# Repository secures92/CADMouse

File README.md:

CADMouse
========

fully 3D printable CAD-Mouse with host software for solidworks.

CAD-Mouse is connected as Joystick. Windows host software translates Axis movements to Solidworks view translation commands.
(Any standard joystick could be use)

Thingiverse: http://www.thingiverse.com/thing:260830
Warning : some parts have been upgraded, check latest version on github.

Video
------
New top spring and added translate / zoom :

Original demo

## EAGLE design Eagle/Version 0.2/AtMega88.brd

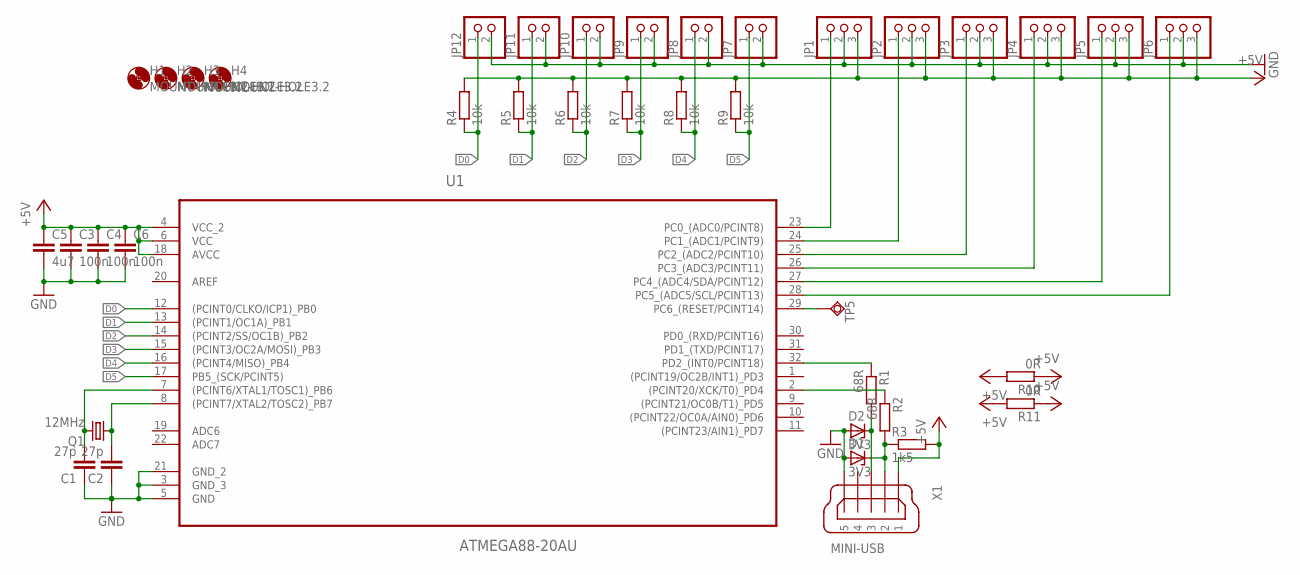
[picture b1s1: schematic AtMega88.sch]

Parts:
C1, C2: 27p; C0805
C3, C4, C6: 100n; C0805
C5: 4u7; C0805
D1, D2: 3V3; SOT23
H1, H2, H3, H4: MOUNT-HOLE3.2; 3,2
JP1, JP2, JP3, JP4, JP5, JP6: PINHD-1X3; 1X03
JP7, JP8, JP9, JP10, JP11, JP12: PINHD-1X2; 1X02
Q1: 12MHz; CSM-7X-DU
R1, R2: 68R; R1206
R3: 1k5; R1206
R4, R5, R6, R7, R8, R9: 10k; R1206
R10, R11: 0R; R1206
TP5: TPSQTP20SQ; TP20SQ
U1: ATMEGA88-20AU; QFP80P900X900X120-32N
X1: MINI-USB; UX60A-MB-5ST

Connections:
+5V: C3.1, C4.1, C5.1, C6.1, JP1.3, JP2.3, JP3.3, JP4.3, JP5.3, JP6.3, R3.2, R4.2, R5.2, R6.2, R7.2, R8.2, R9.2, R10.1, R10.2, R11.1, R11.2, U1.4 (VCC_2), U1.6 (VCC), U1.18 (AVCC), X1.1
A0: JP1.1, U1.23 (PC0_(ADC0/PCINT8))
A1: JP2.1, U1.24 (PC1_(ADC1/PCINT9))
A2: JP3.1, U1.25 (PC2_(ADC2/PCINT10))
A3: JP4.1, U1.26 (PC3_(ADC3/PCINT11))
A4: JP5.1, U1.27 (PC4_(ADC4/SDA/PCINT12))
A5: JP6.1, U1.28 (PC5_(ADC5/SCL/PCINT13))
D0: JP12.1, R4.1, U1.12 ((PCINT0/CLKO/ICP1)_PB0)
D1: JP11.1, R5.1, U1.13 ((PCINT1/OC1A)_PB1)
D2: JP10.1, R6.1, U1.14 ((PCINT2/SS/OC1B)_PB2)
D3: JP9.1, R7.1, U1.15 ((PCINT3/OC2A/MOSI)_PB3)
D4: JP8.1, R8.1, U1.16 ((PCINT4/MISO)_PB4)
D5: JP7.1, R9.1, U1.17 (PB5_(SCK/PCINT5))
GND: C1.1, C2.1, C3.2, C4.2, C5.2, C6.2, D1.1 (A), D2.1 (A), JP1.2, JP2.2, JP3.2, JP4.2, JP5.2, JP6.2, JP7.2, JP8.2, JP9.2, JP10.2, JP11.2, JP12.2, U1.3 (GND_3), U1.5 (GND), U1.21 (GND_2), X1.5
unnamed: C1.2, Q1.2, U1.7 ((PCINT6/XTAL1/TOSC1)_PB6)
unnamed: C2.2, Q1.1, U1.8 ((PCINT7/XTAL2/TOSC2)_PB7)
unnamed: R1.1, U1.32 (PD2_(INT0/PCINT18))
unnamed: R2.1, U1.2 ((PCINT20/XCK/T0)_PD4)
unnamed: D2.3 (C), R1.2, X1.3
unnamed: D1.3 (C), R2.2, R3.1, X1.2
unnamed: TP5.TP, U1.29 (PC6_(RESET/PCINT14))

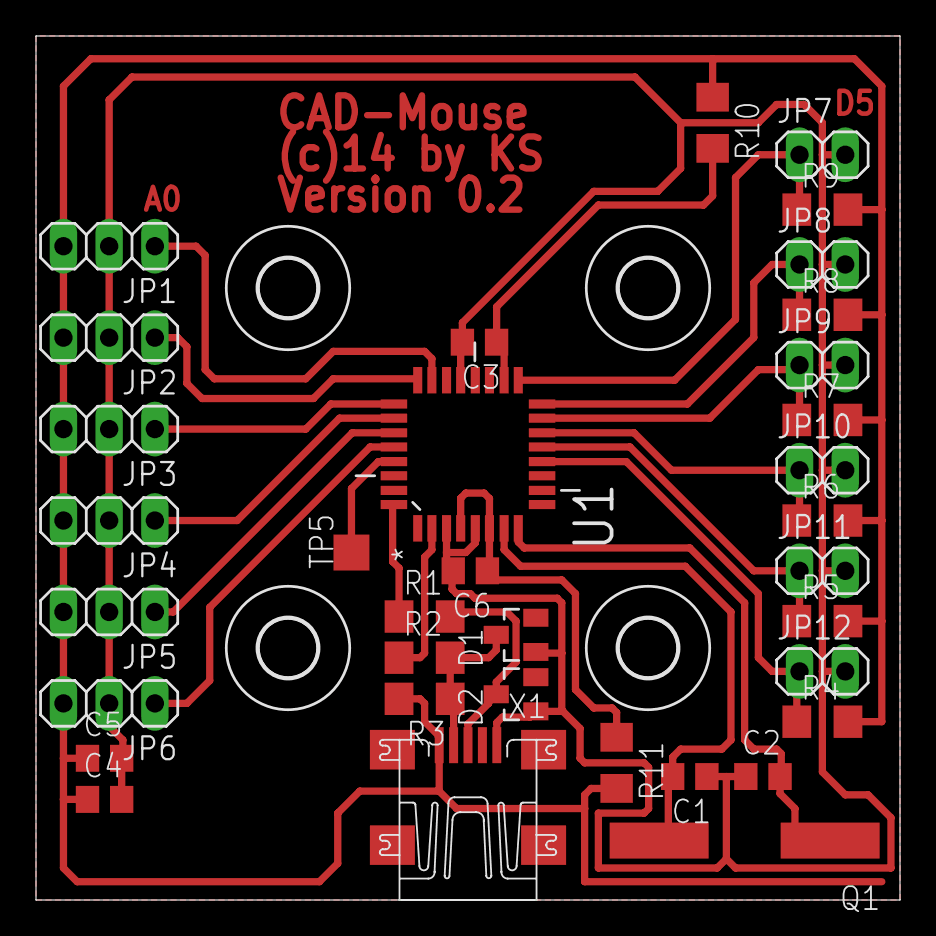
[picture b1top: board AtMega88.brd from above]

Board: 2 copper layers, 48.0 x 48.0 mm, 39 parts (0 on the bottom side), 21 nets.

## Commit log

2014-03-01 init
2014-03-01 media
2014-03-03 Electronics Version 0.2
    Updated Electronics to Version 0.2
2014-05-08 add Z axis to zoom, make it work for every version of solidworks, improve smoothness by increasing refresh rate
2014-05-08 Added compiled file for simplicity and ease of share
2014-05-09 buil manual + SlimDX Runtime
2014-05-09 new top spring with 2 spring instead of 1
2014-05-11 added button support to zoom / translate added model rotation on Z axe added controls to modify threshold value and factor
2014-05-16 new stronger version of spring 0.4 to be use without knob bottom
2014-05-16 upgraded description
2014-05-17 add error management when no joystick is plug or no document open in SW
